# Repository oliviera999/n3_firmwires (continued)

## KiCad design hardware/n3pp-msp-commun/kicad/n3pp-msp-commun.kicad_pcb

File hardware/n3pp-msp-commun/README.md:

# Carte commune n3pp + msp (KiCad)

**Un seul PCB pour deux stations** : la serre/élevage (**n3pp**) et la station météo
(**msp**) partagent cette carte porteuse pour **ESP32 DevKit V1 30 broches**. Les deux
brochages firmware forment une **union disjointe vérifiée** (aucun GPIO utilisé pour deux
usages différents) : les firmwares actuels tournent **sans aucune modification**, c'est le
**profil d'assemblage** (quels composants on soude) qui spécialise la carte.

```
pinmap.json                  Source de vérité (union n3pp_config.h + msp_config.h, profils par broche)
kicad/n3pp-msp-commun.*      Projet KiCad 8 (schéma, PCB ROUTÉ) — ouvrable KiCad 8/9/10
BOM.csv                      Nomenclature (séparateur ;) avec colonne Profil
ACHATS.md                    Liste d'achat complète par profil (BOM + périphériques + boîtier + outillage)
ASSEMBLAGE-N3PP.md           Feuille d'assemblage générée : quoi souder pour une station n3pp
ASSEMBLAGE-MSP.md            Feuille d'assemblage générée : quoi souder pour une station msp
exports/gerbers-*.zip        Fabrication (Gerbers + perçages) — 210 x 105 mm, 2 couches, rev 0.2
exports/schema.pdf, pcb-*.svg   Rendus pour revue sans KiCad
fritzing/*.fzz               Vue breadboard du câblage (Fritzing >= 1.0)
generator/generate.py        Régénère schéma + PCB (non routé) + BOM + feuilles d'assemblage
generator/route_lv.py        Pipeline de routage (freerouting + couture GND + reliefs)
generator/tidy_silkscreen.py  Range la sérigraphie (repères vs étiquettes)
generator/export_fab.py      Export Gerbers/perçages prêts fabricant + rendus
generator/generate_fritzing.py  Régénère le .fzz de câblage
tools/check_pinmap_vs_firmware.py   Garde anti-dérive DOUBLE : n3pp_config.h ET msp_config.h ↔ plan
```

## Le principe : une base, deux profils

| Profil | Composants à souder | Le firmware tourne tel quel ? |
|---|---|---|
| **commun** | DevKit + alim + **interrupteur d'alim capteurs (GPIO13)** + 5 entrées ADC + pont batterie commuté + I2C/OLED + breakout + distribution | — (socle des deux profils) |
| **n3pp** | + REL2 (pompe GPIO12) + DHT GPIO18 | ✅ `pio run -e esp32dev` (n3pp) |
| **msp** | + servos tracker + 2 DHT + DS18B20 + pluie + 10k LDR | ✅ `pio run -e esp32dev` (msp) |
| **extension** | REL3..REL6 (GPIO 16/17/19/23), à activer côté firmware plus tard | provision matérielle |

Aucun strap, aucun interrupteur : les GPIO des deux firmwares ne se marchent jamais
dessus (voir la table ci-dessous), on peuple ou pas. Les feuilles
[`ASSEMBLAGE-N3PP.md`](ASSEMBLAGE-N3PP.md) / [`ASSEMBLAGE-MSP.md`](ASSEMBLAGE-MSP.md)
sont **générées depuis le même code que le PCB** : elles ne peuvent pas dériver du plan.

## Table des broches (union disjointe)

| GPIO | Bloc carte | n3pp (`n3pp_config.h`) | msp (`msp_config.h`) |
|---|---|---|---|
| 13 | **Interrupteur d'alim capteurs** (Q1+Q7 P-MOSFET → rail `+3V3_SW`) | `RELAIS` | `RELAIS` |
| 12 | **REL2** (strapping MTDI → pull-down base 10k) | `POMPE` | — |
| 16/17/19/23 | **REL3..REL6** extensions AUX | — | — |
| 18 | DHT n3pp (JST, pull-up 10k) | `DHTPIN` | — |
| 26 / 15 | DHT INT / EXT (JST, pull-ups 10k) | — | `DHTPININT` / `DHTPINEXT` |
| 2 | 1-Wire DS18B20 (bornier, pull-up 4,7k) ⚠️ strapping | — | `oneWireBus` |
| 27 | Pluie — **sortie DO numérique** (ADC2 ≠ WiFi) | — | `PLUIE` |
| 33/32/35/34/39 | **ADC A..E** (borniers 3V3/AIN/GND) | `humidite1..4`, `LUMINOSITE` | `LUMINOSITEa..d`, `HumiditeSol` |
| 36 (VP) | Pont batterie 2,2k/2,2k (bornier VBAT/GND) | `pontdiv` | `pontdiv` |
| 25 / 14 | Servos tracker (headers, série 220R) | — | `SERVOGD` / `SERVOHB` |
| 21 / 22 | I2C : OLED 0x3C + **3 ports libres** (pull-ups 4,7k) | ✅ | ✅ |
| 4, 5, EN, RX0, TX0 | **Breakout J18** (tous les GPIO restants) | libres | libres |

## Les demandes spécifiques de cette carte

- **Rail capteurs commuté (rev 0.2)** : les deux firmwares utilisent GPIO13 comme
  *power-gate* (mis à 1 au réveil, relâché en deep sleep — vérifié dans les sources).
  La carte le câble sur un **interrupteur haut P-MOSFET** (Q1 BC337 + Q7 NDP6020P) qui
  coupe `+3V3_SW` — capteurs, OLED, ports I2C **et leurs pull-ups** — pendant la veille.
  Le **pont diviseur batterie est commuté lui aussi** (Q8 BS250 côté haut + Q9), donc
  ~0 µA de fuite en veille, et jamais plus de 3,3 V sur GPIO36 pont coupé.
- **5 canaux relais** embarqués (BC337 + 1N4007 + LED témoin + bornier NO/COM/NC) :
  REL2 piloté par n3pp (pompe), REL3..REL6 en réserve sur des GPIO **non-strapping** —
  à activer côté firmware comme AUX1/AUX2 de ffp5cs, sans retoucher la carte.
- **Connexions I2C supplémentaires** : OLED + 3 ports libres (J15/J16/J17, brochage
  GND/VCC/SCL/SDA), 3-4 modules simultanés avec les pull-ups 4,7 k.
- **Toutes les broches restantes utilisables** : breakout J18 (`3V3 GND EN IO4 IO5 RX0
  TX0` — RX0/TX0 à laisser libres pendant un flash USB), rail d'alim Dupont J19
  (2×5V 2×GND 2×3V3), borniers de distribution 5 V (J28) et 3V3 (J29).
- **Zéro soudure à l'usage** : DevKit socketé, charges sur borniers à vis, capteurs sur
  JST-XH/borniers, servos/OLED/GPIO en headers.

## Pièges connus (hérités des firmwares, choix assumés)

- **GPIO2 (1-Wire msp)** est une broche de strapping : le pull-up 4,7 k peut gêner le
  passage en mode flash. Si le flash USB échoue, débrancher la sonde DS18B20 le temps du
  flash. (Conservé pour rester compatible avec le firmware msp actuel.)
- **GPIO27 (pluie msp)** est sur ADC2, inutilisable en analogique quand le WiFi est actif :
  brancher la sortie **DO** (numérique) du module pluie, pas AO — lue en `digitalRead`
  par le firmware msp ≥ 2.72 (projection 4095 sec / 100 mouillé, contrat serveur inchangé).
- **GPIO12 (pompe n3pp)** est strapping MTDI : le pull-down de base du canal REL2 garantit
  l'état sûr au boot.
- **JP1 (cavalier 3V3)** : en alimentation batterie/LDO par J29, RETIRER le cavalier
  avant de brancher l'USB du DevKit (sinon deux régulateurs se disputent le rail).
- Profils **sur batterie (18650 + TP4056 solaire)** : ne pas peupler les LED témoin,
  et **ne jamais brancher la batterie brute sur J1/jack** (brownouts + relais 5 V) —
  boost 5 V → J1 si relais/servos, ou LDO 3,3 V → J29 sinon ; mesure VBAT → J27.
  Câblages, achats et autonomies chiffrées : [`ACHATS.md` §5 bis](ACHATS.md).

## Régénérer / rerouter / vérifier

```bash
cd hardware/n3pp-msp-commun
python3 generator/generate.py          # schéma + PCB placé (NON routé) + BOM + feuilles
python3 generator/route_lv.py          # autoroute, coud les masses, corrige les reliefs
python3 generator/tidy_silkscreen.py   # écarte les repères qui masquent une étiquette
python3 generator/export_fab.py        # zip Gerbers prêt JLCPCB + rendus de revue
python3 tools/check_pinmap_vs_firmware.py   # garde anti-dérive (les DEUX firmwares)
kicad-cli pcb drc --severity-error kicad/n3pp-msp-commun.kicad_pcb -o /tmp/drc.rpt
```

⚠️ `generate.py` écrase le PCB routé — enchaîner systématiquement avec `route_lv.py`.
Le routage livré dans `kicad/` est déjà fait et validé (DRC 0 violation).

Empreintes : bibliothèque officielle KiCad 8.0.9 (CC-BY-SA 4.0 + exception d'usage),
vendorées dans `generator/footprints/`.

Commander les cartes : voir **[../COMMANDE_JLCPCB.md](../COMMANDE_JLCPCB.md)**
(réglages du formulaire, options utiles, pourquoi 1 oz ici et 2 oz sur la 230 V).

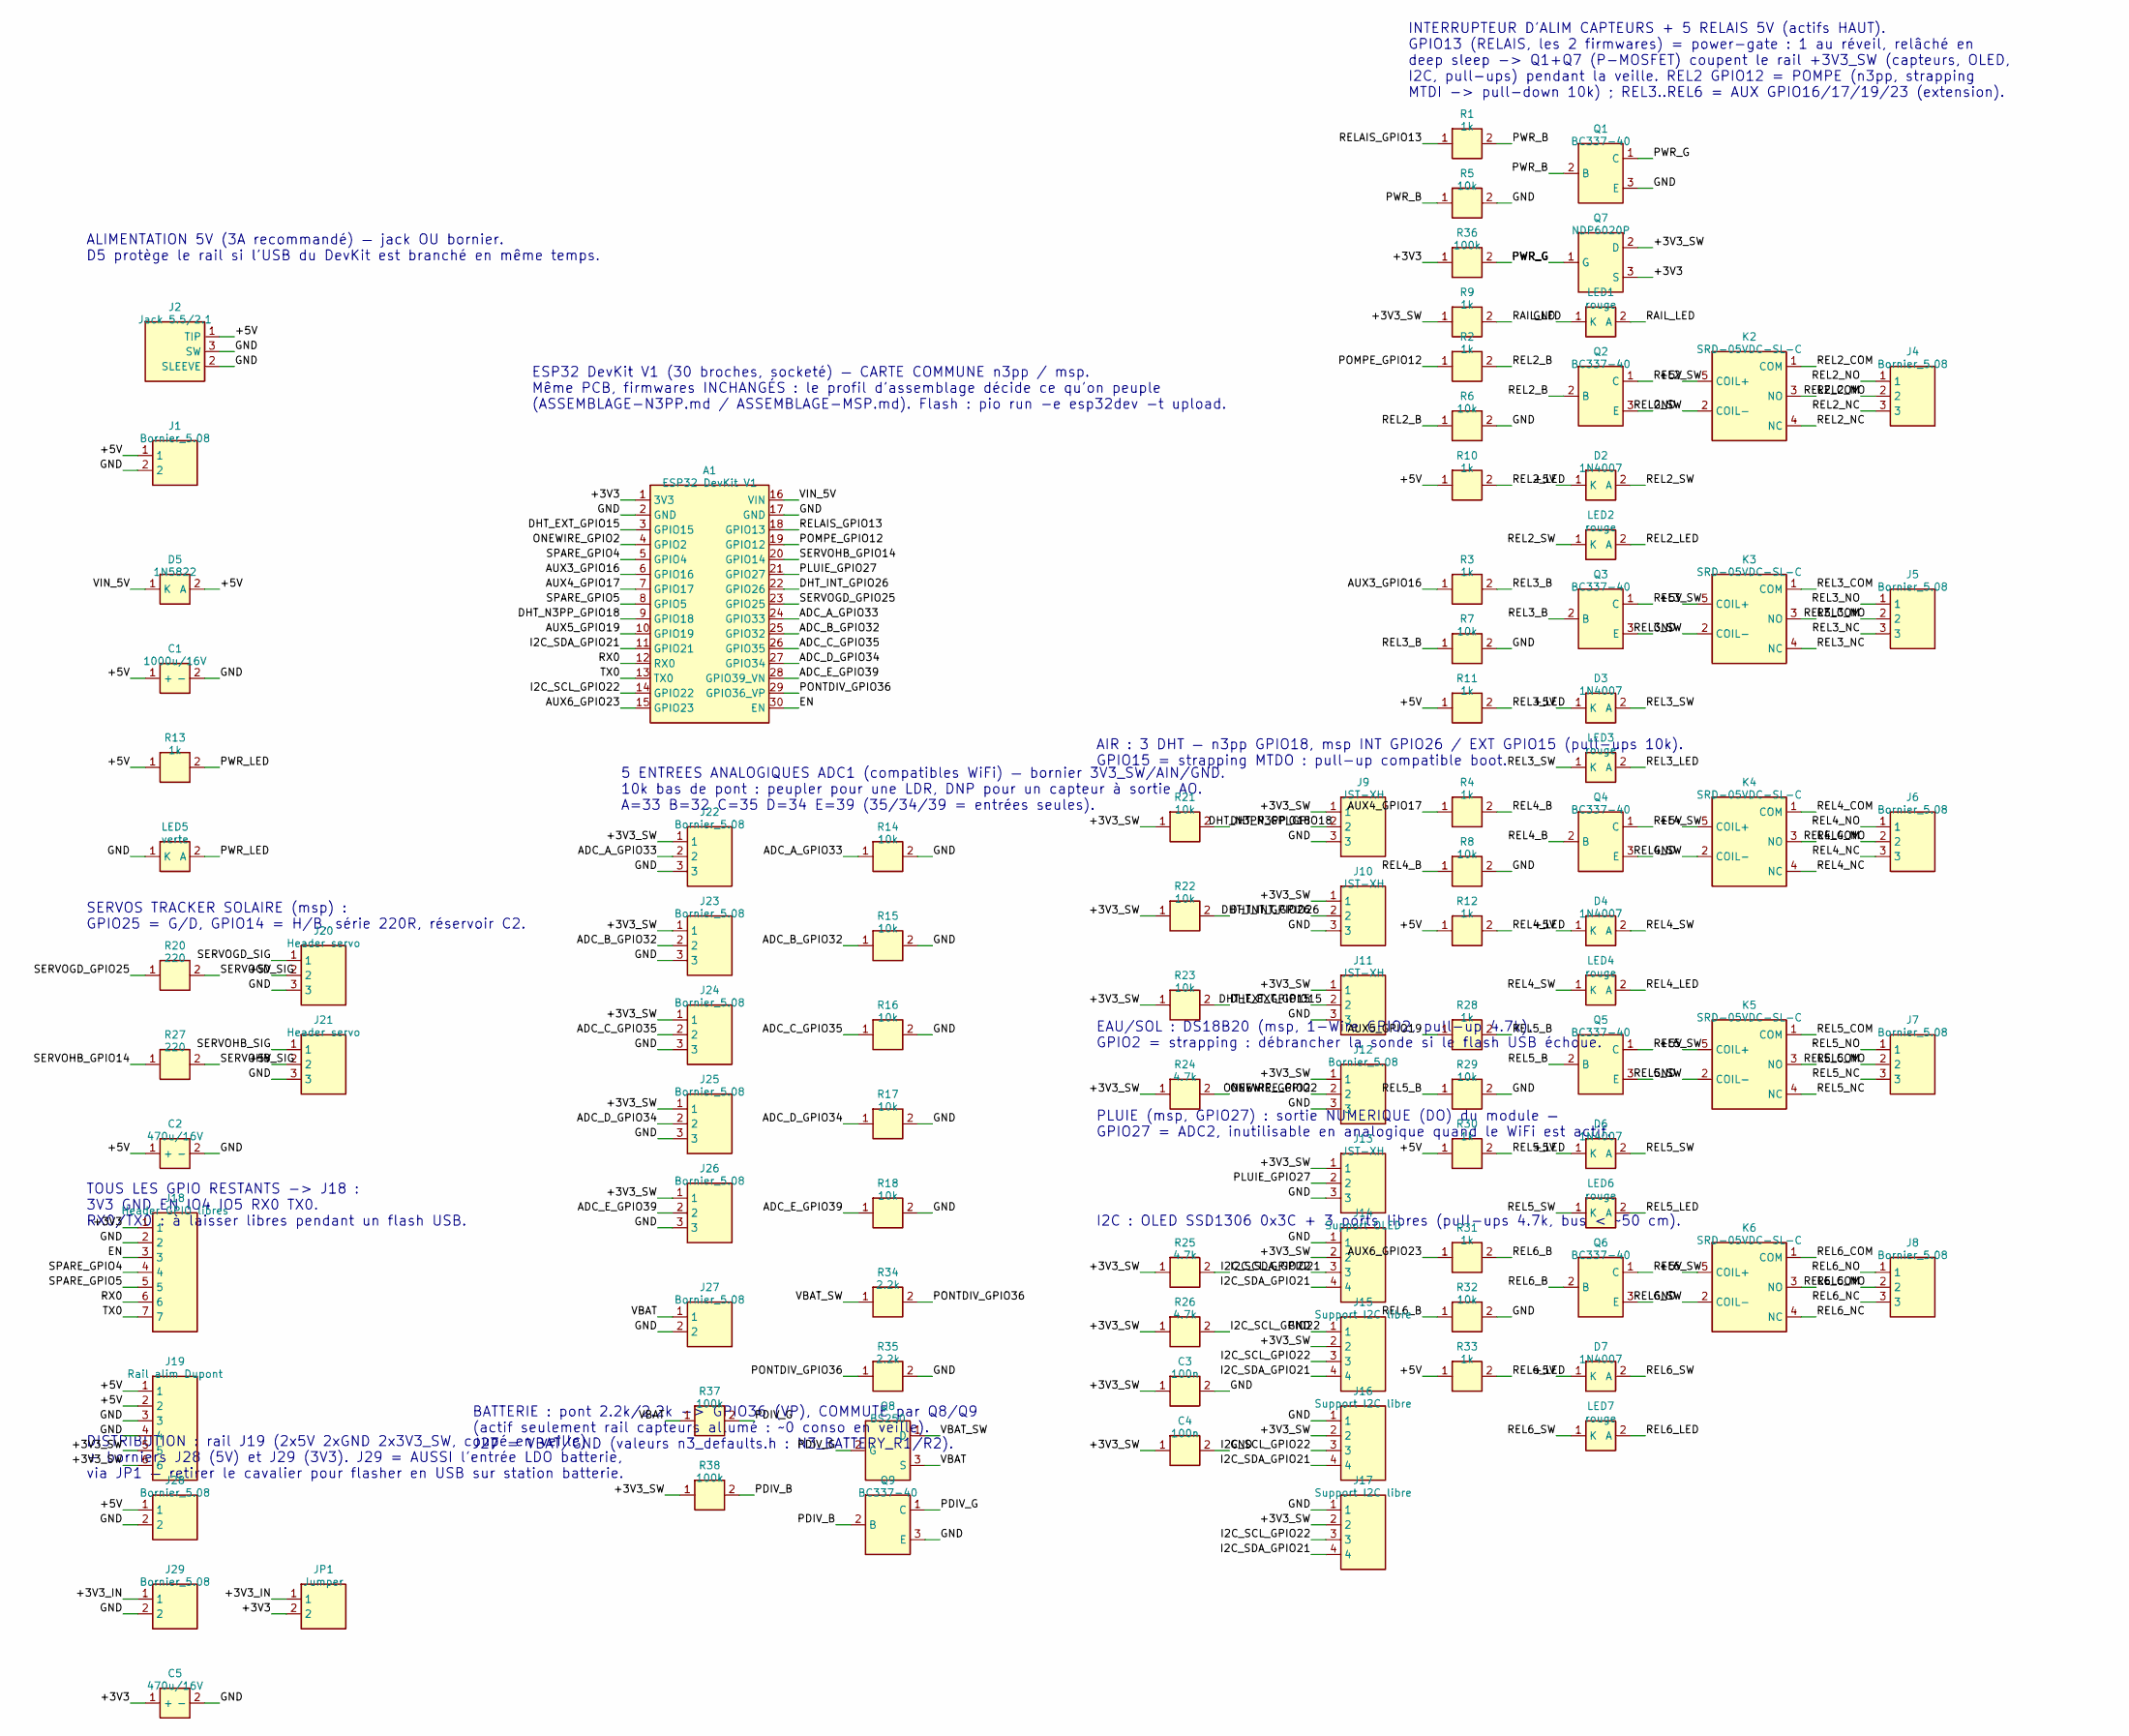
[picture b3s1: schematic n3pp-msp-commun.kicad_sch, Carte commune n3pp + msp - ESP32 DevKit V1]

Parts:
A1: ESP32 DevKit V1; ESP32_DevKit_V1_30pin
C1: 1000u/16V; CP_Radial_D10.0mm_P5.00mm
C2, C5: 470u/16V; CP_Radial_D8.0mm_P3.50mm
C3, C4: 100n; C_Disc_D5.0mm_W2.5mm_P5.00mm
D2, D3, D4, D6, D7: 1N4007; D_DO-41_SOD81_P10.16mm_Horizontal
D5: 1N5822; D_DO-201AD_P15.24mm_Horizontal
J1, J27, J28, J29: Bornier_5.08; TerminalBlock_bornier-2_P5.08mm
J2: Jack 5.5/2.1; BarrelJack_Horizontal
J4, J5, J6, J7, J8, J12, J22, J23, J24, J25, J26: Bornier_5.08; TerminalBlock_bornier-3_P5.08mm
J9, J10, J11, J13: JST-XH; JST_XH_B3B-XH-A_1x03_P2.50mm_Vertical
J14: Support OLED; PinSocket_1x04_P2.54mm_Vertical
J15, J16, J17: Support I2C libre; PinSocket_1x04_P2.54mm_Vertical
J18: Header GPIO libres; PinHeader_1x07_P2.54mm_Vertical
J19: Rail alim Dupont; PinHeader_1x06_P2.54mm_Vertical
J20, J21: Header servo; PinHeader_1x03_P2.54mm_Vertical
JP1: Jumper; PinHeader_1x02_P2.54mm_Vertical
K2, K3, K4, K5, K6: SRD-05VDC-SL-C; Relay_SPDT_SANYOU_SRD_Series_Form_C
LED1, LED2, LED3, LED4, LED6, LED7: rouge; LED_D5.0mm
LED5: verte; LED_D5.0mm
Q1, Q2, Q3, Q4, Q5, Q6, Q9: BC337-40; TO-92_Inline
Q7: NDP6020P; TO-220-3_Vertical
Q8: BS250; TO-92_Inline
R1, R2, R3, R4, R9, R10, R11, R12, R13, R28, R30, R31, R33: 1k; R_Axial_DIN0207_L6.3mm_D2.5mm_P10.16mm_Horizontal
R5, R6, R7, R8, R14, R15, R16, R17, R18, R21, R22, R23, R29, R32: 10k; R_Axial_DIN0207_L6.3mm_D2.5mm_P10.16mm_Horizontal
R20, R27: 220; R_Axial_DIN0207_L6.3mm_D2.5mm_P10.16mm_Horizontal
R24, R25, R26: 4.7k; R_Axial_DIN0207_L6.3mm_D2.5mm_P10.16mm_Horizontal
R34, R35: 2.2k; R_Axial_DIN0207_L6.3mm_D2.5mm_P10.16mm_Horizontal
R36, R37, R38: 100k; R_Axial_DIN0207_L6.3mm_D2.5mm_P10.16mm_Horizontal

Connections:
+3V3: A1.1 (3V3), C5.1 (+), J18.1, JP1.2, Q7.3 (S), R36.1
+3V3_IN: J29.1, JP1.1
+3V3_SW: C3.1, C4.1, J9.1, J10.1, J11.1, J12.1, J13.1, J14.2, J15.2, J16.2, J17.2, J19.5, J19.6, J22.1, J23.1, J24.1, J25.1, J26.1, Q7.2 (D), R9.1, R21.1, R22.1, R23.1, R24.1, R25.1, R26.1, R38.1
+5V: C1.1 (+), C2.1 (+), D2.1 (K), D3.1 (K), D4.1 (K), D5.2 (A), D6.1 (K), D7.1 (K), J1.1, J2.1 (TIP), J19.1, J19.2, J20.2, J21.2, J28.1, K2.5 (COIL+), K3.5 (COIL+), K4.5 (COIL+), K5.5 (COIL+), K6.5 (COIL+), R10.1, R11.1, R12.1, R13.1, R30.1, R33.1
ADC_A_GPIO33: A1.24 (GPIO33), J22.2, R14.1
ADC_B_GPIO32: A1.25 (GPIO32), J23.2, R15.1
ADC_C_GPIO35: A1.26 (GPIO35), J24.2, R16.1
ADC_D_GPIO34: A1.27 (GPIO34), J25.2, R17.1
ADC_E_GPIO39: A1.28 (GPIO39_VN), J26.2, R18.1
AUX3_GPIO16: A1.6 (GPIO16), R3.1
AUX4_GPIO17: A1.7 (GPIO17), R4.1
AUX5_GPIO19: A1.10 (GPIO19), R28.1
AUX6_GPIO23: A1.15 (GPIO23), R31.1
DHT_EXT_GPIO15: A1.3 (GPIO15), J11.2, R23.2
DHT_INT_GPIO26: A1.22 (GPIO26), J10.2, R22.2
DHT_N3PP_GPIO18: A1.9 (GPIO18), J9.2, R21.2
EN: A1.30 (EN), J18.3
GND: A1.2 (GND), A1.17 (GND), C1.2 (-), C2.2 (-), C3.2, C4.2, C5.2 (-), J1.2, J2.2 (SLEEVE), J2.3 (SW), J9.3, J10.3, J11.3, J12.3, J13.3, J14.1, J15.1, J16.1, J17.1, J18.2, J19.3, J19.4, J20.3, J21.3, J22.3, J23.3, J24.3, J25.3, J26.3, J27.2, J28.2, J29.2, LED1.1 (K), LED5.1 (K), Q1.3 (E), Q2.3 (E), Q3.3 (E), Q4.3 (E), Q5.3 (E), Q6.3 (E), Q9.3 (E), R5.2, R6.2, R7.2, R8.2, R14.2, R15.2, R16.2, R17.2, R18.2, R29.2, R32.2, R35.2
I2C_SCL_GPIO22: A1.14 (GPIO22), J14.3, J15.3, J16.3, J17.3, R26.2
I2C_SDA_GPIO21: A1.11 (GPIO21), J14.4, J15.4, J16.4, J17.4, R25.2
ONEWIRE_GPIO2: A1.4 (GPIO2), J12.2, R24.2
PDIV_B: Q9.2 (B), R38.2
PDIV_G: Q8.2 (G), Q9.1 (C), R37.2
PLUIE_GPIO27: A1.21 (GPIO27), J13.2
POMPE_GPIO12: A1.19 (GPIO12), R2.1
PONTDIV_GPIO36: A1.29 (GPIO36_VP), R34.2, R35.1
PWR_B: Q1.2 (B), R1.2, R5.1
PWR_G: Q1.1 (C), Q7.1 (G), R36.2
PWR_LED: LED5.2 (A), R13.2
RAIL_LED: LED1.2 (A), R9.2
REL2_B: Q2.2 (B), R2.2, R6.1
REL2_COM: J4.2, K2.1 (COM)
REL2_LED: LED2.2 (A), R10.2
REL2_NC: J4.3, K2.4 (NC)
REL2_NO: J4.1, K2.3 (NO)
REL2_SW: D2.2 (A), K2.2 (COIL-), LED2.1 (K), Q2.1 (C)
REL3_B: Q3.2 (B), R3.2, R7.1
REL3_COM: J5.2, K3.1 (COM)
REL3_LED: LED3.2 (A), R11.2
REL3_NC: J5.3, K3.4 (NC)
REL3_NO: J5.1, K3.3 (NO)
REL3_SW: D3.2 (A), K3.2 (COIL-), LED3.1 (K), Q3.1 (C)
REL4_B: Q4.2 (B), R4.2, R8.1
REL4_COM: J6.2, K4.1 (COM)
REL4_LED: LED4.2 (A), R12.2
REL4_NC: J6.3, K4.4 (NC)
REL4_NO: J6.1, K4.3 (NO)
REL4_SW: D4.2 (A), K4.2 (COIL-), LED4.1 (K), Q4.1 (C)
REL5_B: Q5.2 (B), R28.2, R29.1
REL5_COM: J7.2, K5.1 (COM)
REL5_LED: LED6.2 (A), R30.2
REL5_NC: J7.3, K5.4 (NC)
REL5_NO: J7.1, K5.3 (NO)
REL5_SW: D6.2 (A), K5.2 (COIL-), LED6.1 (K), Q5.1 (C)
REL6_B: Q6.2 (B), R31.2, R32.1
REL6_COM: J8.2, K6.1 (COM)
REL6_LED: LED7.2 (A), R33.2
REL6_NC: J8.3, K6.4 (NC)
REL6_NO: J8.1, K6.3 (NO)
REL6_SW: D7.2 (A), K6.2 (COIL-), LED7.1 (K), Q6.1 (C)
RELAIS_GPIO13: A1.18 (GPIO13), R1.1
RX0: A1.12 (RX0), J18.6
SERVOGD_GPIO25: A1.23 (GPIO25), R20.1
SERVOGD_SIG: J20.1, R20.2
SERVOHB_GPIO14: A1.20 (GPIO14), R27.1
SERVOHB_SIG: J21.1, R27.2
SPARE_GPIO4: A1.5 (GPIO4), J18.4
SPARE_GPIO5: A1.8 (GPIO5), J18.5
TX0: A1.13 (TX0), J18.7
VBAT: J27.1, Q8.3 (S), R37.1
VBAT_SW: Q8.1 (D), R34.1
VIN_5V: A1.16 (VIN), D5.1 (K)

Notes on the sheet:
ALIMENTATION 5V (3A recommandé) — jack OU bornier. D5 protège le rail si l'USB du DevKit est branché en même temps.
ESP32 DevKit V1 (30 broches, socketé) — CARTE COMMUNE n3pp / msp. Même PCB, firmwares INCHANGÉS : le profil d'assemblage décide ce qu'on peuple (ASSEMBLAGE-N3PP.md / ASSEMBLAGE-MSP.md). Flash : pio run -e esp32dev -t upload.
5 ENTREES ANALOGIQUES ADC1 (compatibles WiFi) — bornier 3V3_SW/AIN/GND. 10k bas de pont : peupler pour une LDR, DNP pour un capteur à sortie AO. A=33 B=32 C=35 D=34 E=39 (35/34/39 = entrées seules).
BATTERIE : pont 2.2k/2.2k -> GPIO36 (VP), COMMUTE par Q8/Q9 (actif seulement rail capteurs allumé : ~0 conso en veille). J27 = VBAT/GND (valeurs n3_defaults.h : N3_BATTERY_R1/R2).
SERVOS TRACKER SOLAIRE (msp) : GPIO25 = G/D, GPIO14 = H/B, série 220R, réservoir C2.
TOUS LES GPIO RESTANTS -> J18 : 3V3 GND EN IO4 IO5 RX0 TX0. RX0/TX0 : à laisser libres pendant un flash USB.
DISTRIBUTION : rail J19 (2x5V 2xGND 2x3V3_SW, coupé en veille) + borniers J28 (5V) et J29 (3V3). J29 = AUSSI l'entrée LDO batterie, via JP1 — retirer le cavalier pour flasher en USB sur station batterie.
AIR : 3 DHT — n3pp GPIO18, msp INT GPIO26 / EXT GPIO15 (pull-ups 10k). GPIO15 = strapping MTDO : pull-up compatible boot.
EAU/SOL : DS18B20 (msp, 1-Wire GPIO2, pull-up 4.7k). GPIO2 = strapping : débrancher la sonde si le flash USB échoue.
PLUIE (msp, GPIO27) : sortie NUMERIQUE (DO) du module — GPIO27 = ADC2, inutilisable en analogique quand le WiFi est actif.
I2C : OLED SSD1306 0x3C + 3 ports libres (pull-ups 4.7k, bus < ~50 cm).
INTERRUPTEUR D'ALIM CAPTEURS + 5 RELAIS 5V (actifs HAUT). GPIO13 (RELAIS, les 2 firmwares) = power-gate : 1 au réveil, relâché en deep sleep -> Q1+Q7 (P-MOSFET) coupent le rail +3V3_SW (capteurs, OLED, I2C, pull-ups) pendant la veille. REL2 GPIO12 = POMPE (n3pp, strapping MTDI -> pull-down 10k) ; R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

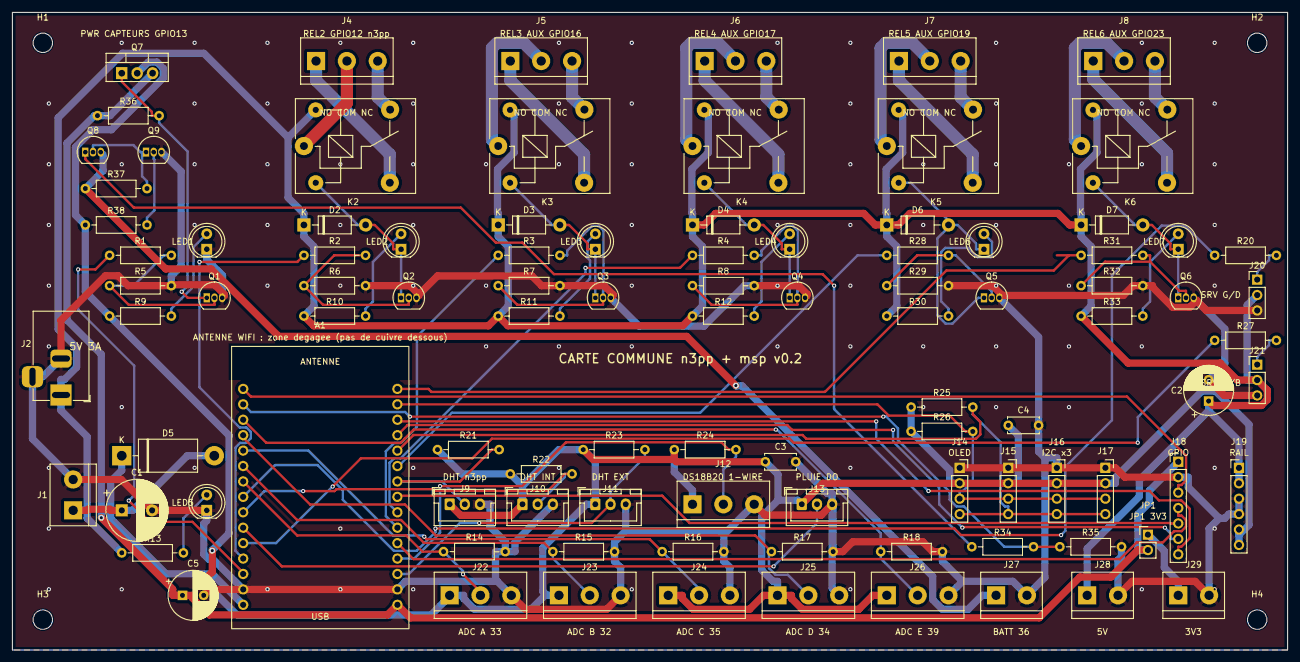
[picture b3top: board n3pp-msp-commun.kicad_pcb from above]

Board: 2 copper layers, 210.0 x 105.0 mm, 103 parts (0 on the bottom side), 72 nets.

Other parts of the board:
H1, H2, H3, H4: M3; MountingHole_3.2mm_M3

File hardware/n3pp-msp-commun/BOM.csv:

Refs;Qte;Valeur;Empreinte;Description;Profil
A1;1;ESP32 DevKit V1;ESP32_DevKit_V1_30pin;Module ESP32-WROOM-32 DevKit V1 30 broches, sur 2 supports 1x15;commun (toujours)
C1;1;1000u/16V;CP_Radial_D10.0mm_P5.00mm;Réservoir rail 5V (relais + servos + WiFi);commun (toujours)
C2;1;470u/16V;CP_Radial_D8.0mm_P3.50mm;Découplage rail 5V servos;profil msp
C3;1;100n;C_Disc_D5.0mm_W2.5mm_P5.00mm;Découplage 3V3 capteurs;commun (toujours)
C4;1;100n;C_Disc_D5.0mm_W2.5mm_P5.00mm;Découplage 3V3 I2C;commun (toujours)
D1;1;1N4007;D_DO-41_SOD81_P10.16mm_Horizontal;Diode de roue libre bobine;commun (toujours)
D2;1;1N4007;D_DO-41_SOD81_P10.16mm_Horizontal;Diode de roue libre bobine;profil n3pp
D3 D4 D6 D7;4;1N4007;D_DO-41_SOD81_P10.16mm_Horizontal;Diode de roue libre bobine;extension (option)
D5;1;1N5822;D_DO-201AD_P15.24mm_Horizontal;Schottky 3A vers VIN DevKit (anti-retour si USB branché);commun (toujours)
H1 H2 H3 H4;4;M3;MountingHole_3.2mm_M3;Trou de fixation M3;commun (toujours)
J1;1;Bornier_5.08;TerminalBlock_bornier-2_P5.08mm;Entrée 5V alternative (bornier, 1=+5V 2=GND);commun (toujours)
J10;1;JST-XH;JST_XH_B3B-XH-A_1x03_P2.50mm_Vertical;DHT INT msp (1=3V3 2=DATA 3=GND);profil msp
J11;1;JST-XH;JST_XH_B3B-XH-A_1x03_P2.50mm_Vertical;DHT EXT msp (1=3V3 2=DATA 3=GND);profil msp
J12;1;Bornier_5.08;TerminalBlock_bornier-3_P5.08mm;Sonde DS18B20 étanche (1=3V3 2=DATA 3=GND);profil msp
J13;1;JST-XH;JST_XH_B3B-XH-A_1x03_P2.50mm_Vertical;Capteur pluie — sortie NUMERIQUE DO (1=3V3 2=DO 3=GND);profil msp
J14;1;Support OLED;PinSocket_1x04_P2.54mm_Vertical;OLED SSD1306 128x64 I2C 0x3C (1=GND 2=VCC 3=SCL 4=SDA);commun (toujours)
J15;1;Support I2C libre;PinSocket_1x04_P2.54mm_Vertical;Port I2C libre 1 (1=GND 2=VCC 3=SCL 4=SDA);commun (toujours)
J16;1;Support I2C libre;PinSocket_1x04_P2.54mm_Vertical;Port I2C libre 2 (1=GND 2=VCC 3=SCL 4=SDA);commun (toujours)
J17;1;Support I2C libre;PinSocket_1x04_P2.54mm_Vertical;Port I2C libre 3 (1=GND 2=VCC 3=SCL 4=SDA);commun (toujours)
J18;1;Header GPIO libres;PinHeader_1x07_P2.54mm_Vertical;GPIO libres (1=3V3 2=GND 3=EN 4=IO4 5=IO5 6=RX0 7=TX0);commun (toujours)
J19;1;Rail alim Dupont;PinHeader_1x06_P2.54mm_Vertical;Rail alim modules (1=5V 2=5V 3=GND 4=GND 5=3V3 6=3V3);commun (toujours)
J2;1;Jack 5.5/2.1;BarrelJack_Horizontal;Entrée 5V 3A (jack, centre = +);commun (toujours)
J20;1;Header servo;PinHeader_1x03_P2.54mm_Vertical;Servo G/D tracker (1=SIG 2=+5V 3=GND);profil msp
J21;1;Header servo;PinHeader_1x03_P2.54mm_Vertical;Servo H/B tracker (1=SIG 2=+5V 3=GND);profil msp
J22;1;Bornier_5.08;TerminalBlock_bornier-3_P5.08mm;Entrée ADC_A (1=3V3 2=AIN 3=GND) — n3pp: humidite1 (sol) / msp: LUMINOSITEa (LDR);commun (toujours)
J23;1;Bornier_5.08;TerminalBlock_bornier-3_P5.08mm;Entrée ADC_B (1=3V3 2=AIN 3=GND) — n3pp: humidite2 (sol) / msp: HumiditeSol (module AO);commun (toujours)
J24;1;Bornier_5.08;TerminalBlock_bornier-3_P5.08mm;Entrée ADC_C (1=3V3 2=AIN 3=GND) — n3pp: humidite3 (sol) / msp: LUMINOSITEc (LDR);commun (toujours)
J25;1;Bornier_5.08;TerminalBlock_bornier-3_P5.08mm;Entrée ADC_D (1=3V3 2=AIN 3=GND) — n3pp: humidite4 (sol) / msp: LUMINOSITEb (LDR);commun (toujours)
J26;1;Bornier_5.08;TerminalBlock_bornier-3_P5.08mm;Entrée ADC_E (1=3V3 2=AIN 3=GND) — n3pp: LUMINOSITE (LDR) / msp: LUMINOSITEd (LDR);commun (toujours)
J27;1;Bornier_5.08;TerminalBlock_bornier-2_P5.08mm;Mesure batterie (1=VBAT 2=GND, pont 2.2k/2.2k -> GPIO36);commun (toujours)
J28;1;Bornier_5.08;TerminalBlock_bornier-2_P5.08mm;Distribution 5V (1=+5V 2=GND);commun (toujours)
J29;1;Bornier_5.08;TerminalBlock_bornier-2_P5.08mm;Distribution 3V3 (1=+3V3 2=GND);commun (toujours)
J3;1;Bornier_5.08;TerminalBlock_bornier-3_P5.08mm;Bornier charge (1=NO 2=COM 3=NC);commun (toujours)
J4;1;Bornier_5.08;TerminalBlock_bornier-3_P5.08mm;Bornier charge (1=NO 2=COM 3=NC);profil n3pp
J5 J6 J7 J8;4;Bornier_5.08;TerminalBlock_bornier-3_P5.08mm;Bornier charge (1=NO 2=COM 3=NC);extension (option)
J9;1;JST-XH;JST_XH_B3B-XH-A_1x03_P2.50mm_Vertical;DHT n3pp (1=3V3 2=DATA 3=GND);profil n3pp
K1;1;SRD-05VDC-SL-C;Relay_SPDT_SANYOU_SRD_Series_Form_C;Relais 5V SPDT 10A (Songle/Sanyou SRD);commun (toujours)
K2;1;SRD-05VDC-SL-C;Relay_SPDT_SANYOU_SRD_Series_Form_C;Relais 5V SPDT 10A (Songle/Sanyou SRD);profil n3pp
K3 K4 K5 K6;4;SRD-05VDC-SL-C;Relay_SPDT_SANYOU_SRD_Series_Form_C;Relais 5V SPDT 10A (Songle/Sanyou SRD);extension (option)
LED1;1;rouge;LED_D5.0mm;LED témoin relais ON (DNP si profil batterie);commun (toujours)
LED2;1;rouge;LED_D5.0mm;LED témoin relais ON (DNP si profil batterie);profil n3pp
LED3 LED4 LED6 LED7;4;rouge;LED_D5.0mm;LED témoin relais ON (DNP si profil batterie);extension (option)
LED5;1;verte;LED_D5.0mm;LED présence 5V (DNP si profil batterie);commun (toujours)
Q1;1;BC337-40;TO-92_Inline;Transistor NPN commande relais (1=C 2=B 3=E);commun (toujours)
Q2;1;BC337-40;TO-92_Inline;Transistor NPN commande relais (1=C 2=B 3=E);profil n3pp
Q3 Q4 Q5 Q6;4;BC337-40;TO-92_Inline;Transistor NPN commande relais (1=C 2=B 3=E);extension (option)
R1;1;1k;R_Axial_DIN0207_L6.3mm_D2.5mm_P10.16mm_Horizontal;Résistance base transistor;commun (toujours)
R10;1;1k;R_Axial_DIN0207_L6.3mm_D2.5mm_P10.16mm_Horizontal;Résistance LED témoin (DNP si profil batterie);profil n3pp
R11 R12 R30 R33;4;1k;R_Axial_DIN0207_L6.3mm_D2.5mm_P10.16mm_Horizontal;Résistance LED témoin (DNP si profil batterie);extension (option)
R13;1;1k;R_Axial_DIN0207_L6.3mm_D2.5mm_P10.16mm_Horizontal;Résistance LED présence 5V (DNP si profil batterie);commun (toujours)
R14;1;10k;R_Axial_DIN0207_L6.3mm_D2.5mm_P10.16mm_Horizontal;"Bas de pont ADC_A (peupler si LDR ; DNP si capteur AO)";profil msp
R15;1;10k;R_Axial_DIN0207_L6.3mm_D2.5mm_P10.16mm_Horizontal;"Bas de pont ADC_B (peupler si LDR ; DNP si capteur AO)";extension (option)
R16;1;10k;R_Axial_DIN0207_L6.3mm_D2.5mm_P10.16mm_Horizontal;"Bas de pont ADC_C (peupler si LDR ; DNP si capteur AO)";profil msp
R17;1;10k;R_Axial_DIN0207_L6.3mm_D2.5mm_P10.16mm_Horizontal;"Bas de pont ADC_D (peupler si LDR ; DNP si capteur AO)";profil msp
R18;1;10k;R_Axial_DIN0207_L6.3mm_D2.5mm_P10.16mm_Horizontal;"Bas de pont ADC_E (peupler si LDR ; DNP si capteur AO)";commun (toujours)
R2;1;1k;R_Axial_DIN0207_L6.3mm_D2.5mm_P10.16mm_Horizontal;Résistance base transistor;profil n3pp
R20;1;220;R_Axial_DIN0207_L6.3mm_D2.5mm_P10.16mm_Horizontal;Série signal servo G/D (GPIO25);profil msp
R21;1;10k;R_Axial_DIN0207_L6.3mm_D2.5mm_P10.16mm_Horizontal;Pull-up data DHT n3pp;profil n3pp
R22;1;10k;R_Axial_DIN0207_L6.3mm_D2.5mm_P10.16mm_Horizontal;Pull-up data DHT INT msp;profil msp
R23;1;10k;R_Axial_DIN0207_L6.3mm_D2.5mm_P10.16mm_Horizontal;Pull-up data DHT EXT msp;profil msp
R24;1;4.7k;R_Axial_DIN0207_L6.3mm_D2.5mm_P10.16mm_Horizontal;Pull-up bus 1-Wire DS18B20;profil msp
R25;1;4.7k;R_Axial_DIN0207_L6.3mm_D2.5mm_P10.16mm_Horizontal;Pull-up I2C SDA;commun (toujours)
R26;1;4.7k;R_Axial_DIN0207_L6.3mm_D2.5mm_P10.16mm_Horizontal;Pull-up I2C SCL;commun (toujours)
R27;1;220;R_Axial_DIN0207_L6.3mm_D2.5mm_P10.16mm_Horizontal;Série signal servo H/B (GPIO14);profil msp
R28 R3 R31 R4;4;1k;R_Axial_DIN0207_L6.3mm_D2.5mm_P10.16mm_Horizontal;Résistance base transistor;extension (option)
R34;1;2.2k;R_Axial_DIN0207_L6.3mm_D2.5mm_P10.16mm_Horizontal;Pont batterie haut (N3_BATTERY_R1=2200);commun (toujours)
R35;1;2.2k;R_Axial_DIN0207_L6.3mm_D2.5mm_P10.16mm_Horizontal;Pont batterie bas (N3_BATTERY_R2=2180, 2.2k mesurée);commun (toujours)
R5;1;10k;R_Axial_DIN0207_L6.3mm_D2.5mm_P10.16mm_Horizontal;Pull-down base (état sûr au boot);commun (toujours)
R6;1;10k;R_Axial_DIN0207_L6.3mm_D2.5mm_P10.16mm_Horizontal;Pull-down base (état sûr au boot);profil n3pp
R29 R32 R7 R8;4;10k;R_Axial_DIN0207_L6.3mm_D2.5mm_P10.16mm_Horizontal;Pull-down base (état sûr au boot);extension (option)
R9;1;1k;R_Axial_DIN0207_L6.3mm_D2.5mm_P10.16mm_Horizontal;Résistance LED témoin (DNP si profil batterie);commun (toujours)
A1 (supports);2;Support femelle 1x15 P2.54;monte sur l'empreinte ESP32_DevKit_V1_30pin;Barrettes femelles 15 pts : le DevKit s'enfiche, jamais soudé;commun (toujours)

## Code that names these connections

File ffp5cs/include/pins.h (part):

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constexpr int ONE_WIRE_BUS = 41;  // Bus DS18B20 (37 = conflit PSRAM octale)

// I2C (Wire)
constexpr int I2C_SDA = 8;
constexpr int I2C_SCL = 9;

// OLED Display (I2C)
constexpr int OLED_SDA = I2C_SDA;
constexpr int OLED_SCL = I2C_SCL;
constexpr int OLED_ADDR = 0x3C;

// RTC DS3231 (I2C) - optionnel, pour heure précise offline
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
// SD carte (SPI) - optionnel ; broches NON câblées sur la carte porteuse
// (conservées pour compiler le support SD, à câbler via J20 le cas échéant)
constexpr int SD_CS_PIN   = 10;
constexpr int SD_MOSI_PIN = 11;
constexpr int SD_CLK_PIN  = 12;
constexpr int SD_MISO_PIN = 14;

} // namespace Pins

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// Source de vérité : pinmap_universel_propose.json. SD native (10/12/13/14),
// K5/K6 (=AUX1/AUX2) embarqués : GPIO 48 (LED RGB v1.0 : recopie d'état K5,
// cosmétique) et 45 (strapping VDD_SPI : commande via base 1k + pull-down 10k,
// sûre au boot, comme GPIO2/15 sur les cartes historiques).
namespace Pins {
constexpr int ULTRASON_AQUA = 39;  // net US1
constexpr int ULTRASON_TANK = 40;  // net US2
constexpr int ULTRASON_POTA = 41;  // net US3

constexpr int EAU_POTAGER = ULTRASON_POTA; // Alias pour rétrocompatibilité
constexpr int LUMINOSITE = 6;      // net ADC_E (ADC1_CH5)

constexpr int POMPE_AQUA   = 15;   // net K1
constexpr int POMPE_RESERV = 16;   // net K2
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constexpr int AUX1 = 48;           // net AUX1 (K5)
constexpr int AUX2 = 45;           // net AUX2 (K6)

constexpr int SERVO_GROS   = 21;   // net SERVO1
constexpr int SERVO_PETITS = 47;   // net SERVO2

constexpr int DHT_PIN      = 38;   // net DHT_INT (LED RGB v1.1 : scintillement cosmétique)
constexpr int ONE_WIRE_BUS = 42;   // net ONEWIRE

constexpr int I2C_SDA = 8;
constexpr int I2C_SCL = 9;
constexpr int OLED_SDA = I2C_SDA;
constexpr int OLED_SCL = I2C_SCL;
constexpr int OLED_ADDR = 0x3C;
constexpr uint8_t DS3231_I2C_ADDR = 0x68;

// microSD embarquée (slot bi-site de la carte, côté A2)
constexpr int SD_CS_PIN   = 10;
constexpr int SD_MOSI_PIN = 12;
constexpr int SD_CLK_PIN  = 13;
constexpr int SD_MISO_PIN = 14;

} // namespace Pins

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namespace Pins {
constexpr int ULTRASON_AQUA = 4;   // net US1 (partagé PLUIE msp)
constexpr int ULTRASON_TANK = 5;   // net US2 (partagé DHT_EXT msp)
constexpr int ULTRASON_POTA = 14;  // net US3 (= SD_CS en env wroom-sd)

constexpr int EAU_POTAGER = ULTRASON_POTA;
constexpr int LUMINOSITE = 36;     // net ADC_E (entrée seule, ADC1)

constexpr int POMPE_AQUA   = 16;   // net K1 (partagé POMPE n3pp)
constexpr int POMPE_RESERV = 17;   // net K2
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constexpr int AUX1 = 23;           // net AUX1 (K5)
constexpr int AUX2 = 25;           // net AUX2 (K6)

constexpr int SERVO_GROS   = 26;   // net SERVO1 (partagé SERVOGD msp)
constexpr int SERVO_PETITS = 27;   // net SERVO2 (partagé SERVOHB msp)

constexpr int DHT_PIN      = 15;   // net DHT_INT (commun aux 3 firmwares)
constexpr int ONE_WIRE_BUS = 2;    // net ONEWIRE (partagé TempEau msp)

constexpr int I2C_SDA = 21;
constexpr int I2C_SCL = 22;
constexpr int OLED_SDA = I2C_SDA;
constexpr int OLED_SCL = I2C_SCL;
constexpr int OLED_ADDR = 0x3C;
constexpr uint8_t DS3231_I2C_ADDR = 0x68;

// microSD (option env wroom-sd uniquement — lignes sur US3/AUX1/AUX2 + 12)
constexpr int SD_CS_PIN   = 14;
constexpr int SD_CLK_PIN  = 23;
constexpr int SD_MOSI_PIN = 25;
constexpr int SD_MISO_PIN = 12;    // strapping MTDI : ligne SANS pull-up sur la carte

} // namespace Pins

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constexpr int ONE_WIRE_BUS = 37;  // Bus DS18B20

// I2C (Wire) - Pins par défaut pour ESP32-S3 devkit. Vérifier câblage (VCC/GND/SDA/SCL) et pull-ups si OLED erratique (voir i2c_bus.cpp).
constexpr int I2C_SDA = 8;  // GPIO 8 (SDA)
constexpr int I2C_SCL = 9;  // GPIO 9 (SCL)

// OLED Display (I2C)
constexpr int OLED_SDA = I2C_SDA;
constexpr int OLED_SCL = I2C_SCL;
constexpr int OLED_ADDR = 0x3C;  // Adresse I2C de l'OLED

// RTC DS3231 (I2C) - optionnel, pour heure précise offline
constexpr uint8_t DS3231_I2C_ADDR = 0x68;

// SD carte (SPI) - optionnel, broches 10/11/12/14 (libres, non utilisées par les servos)
constexpr int SD_CS_PIN   = 10;
constexpr int SD_MOSI_PIN = 11;
constexpr int SD_CLK_PIN  = 12;
constexpr int SD_MISO_PIN = 14;

} // namespace Pins

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constexpr int ONE_WIRE_BUS = 26;

// I2C (Wire) - Pins par défaut pour ESP32. Vérifier câblage (VCC/GND/SDA/SCL) et pull-ups si OLED erratique (voir i2c_bus.cpp).
constexpr int I2C_SDA = 21;  // GPIO 21 (SDA)
constexpr int I2C_SCL = 22;  // GPIO 22 (SCL)

// OLED Display (I2C)
constexpr int OLED_SDA = I2C_SDA;
constexpr int OLED_SCL = I2C_SCL;
constexpr int OLED_ADDR = 0x3C;  // Adresse I2C de l'OLED

// RTC DS3231 (I2C) - optionnel, pour heure précise offline
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
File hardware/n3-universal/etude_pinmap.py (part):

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    "US2":      {"ffp5cs": "ULTRASON_TANK", "msp": "DHT_EXT (legacy, préférer BME280 0x77)"},
    "US3":      {"ffp5cs": "ULTRASON_POTA"},
    # capteurs partout
    "DHT_INT":  {"msp": "DHTPININT", "n3pp": "DHT", "ffp5cs": "DHT_PIN"},
    "ONEWIRE":  {"msp": "TempEau (DS18B20)", "ffp5cs": "DS18B20"},
    # power-gate (rail +3V3_SW) — bypass fermé par défaut (jumper) pour ffp5cs
    "GATE":     {"msp": "RELAIS (gate)", "n3pp": "RELAIS (gate)"},
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# ESP32-S3-DevKitC-1 44p — politique STRICTE puis PRAGMATIQUE
S3_ALL = {1, 2, 3, 4, 5, 6, 7, 8, 9, 10, 11, 12, 13, 14, 15, 16, 17, 18, 21,
          38, 39, 40, 41, 42, 45, 47, 48}
S3_ADC1 = set(range(1, 11))            # ADC1 = GPIO1..10 (ADC2 inutilisable WiFi)
S3_STRICT_EXCLUDE = {3, 45, 38, 48, 11}    # strapping (3/45), LED RGB (38/48), 11 = réserve non câblée
S3_PRAGMATIC_CAVEATS = {
    3:  "strapping JTAG-sel (sans effet hors eFuse JTAG) ; pas de pull-up sur la broche (R34 1k → base Q8)",
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# Variante « WROOM + SD universelle » : le slot microSD (unique, câblé en dur)
# monte sur des nets que msp et n3pp N'UTILISENT PAS — ils gardent donc TOUTES
# leurs fonctions, SD comprise, sans arbitrage :
#   SD_CS   = GPIO14 (net US3 — ultrason potager, ffp5cs seulement)
#   SD_CLK  = GPIO23 (net AUX1 — breakout, ffp5cs seulement)
#   SD_MOSI = GPIO25 (net AUX2 — breakout, ffp5cs seulement)
#   SD_MISO = GPIO12 (broche libre ; strapping MTDI : AUCUN pull-up, socket nu)
# Seul ffp5cs-sur-WROOM doit choisir, PAR ENV DE BUILD (mécanisme PINMAP_* déjà
# en place) : env « wroom-sd » = SD active, renonce à US_POTA + AUX1/AUX2 ;
# env standard = 3 ultrasons + AUX, pas de SD. ffp5cs-sur-S3 n'arbitre rien
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NETS_WROOM_SD["AUX2"].update({"msp": "SD_MOSI (option SD)", "n3pp": "SD_MOSI (option SD)"})
NETS_WROOM_SD["AUX2"]["ffp5cs"] = "AUX2 — ou SD_MOSI en env wroom-sd"
NETS_WROOM_SD["SD_MISO"] = {"msp": "SD_MISO", "n3pp": "SD_MISO",
                            "ffp5cs": "SD_MISO (GPIO12 : AUCUN pull-up, socket nu)"}
WROOM_SD_OPTION = {"SD_MISO": 12}

WROOM_MAP = {
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    "SERVO1": 26, "SERVO2": 27,
    "US1": 4, "US2": 5, "US3": 14,
    "DHT_INT": 15, "ONEWIRE": 2, "GATE": 13,
    # SD : absente du site WROOM (S3 uniquement) ; GPIO12 reste libre (header)
}
S3_MAP = {
    "I2C_SDA": 8, "I2C_SCL": 9,
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    "SERVO1": 21, "SERVO2": 47,
    "US1": 39, "US2": 40, "US3": 41,
    "ONEWIRE": 42,
    "GATE": 3,          # JTAG inutilisé ; R35 tire la grille de Q7 → rail +3V3_SW OFF au boot tant que GPIO3 n'est pas HAUT (ou JP1 fermé)
    "DHT_INT": 38,      # caveat LED v1.1 (cosmétique)
    "AUX1": 48,         # caveat LED v1.0 (cosmétique, breakout)
    "AUX2": 45,         # caveat strapping : entrée de module relais SANS pull-up
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
## Addendum audit final rev 0.1 (2026-08-27)

- **GPIO12/MTDI + module microSD (WROOM)** : la précaution « socket nu, aucun
  pull-up » ne couvre pas un module ENFICHÉ avec carte : le pull-up interne DAT0
  de la carte SD (et a fortiori un module tamponné type Catalex) peut tirer MTDI
  haut à l'échantillonnage du strap → VDD_SDIO 1,8 V, boot en échec. Consigne :
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
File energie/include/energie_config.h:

#pragma once
/**
 * Banc d'essai energie — configuration (ESP32-S3 + 3 x INA226).
 *
 * Voies : panneau solaire (production), batterie plomb/AGM 12 V (charge /
 * decharge), consommation des peripheriques. Shunt, courant max, sens et gain
 * sont reglables ici ET a chaud par la console serie (persistes en NVS).
 *
 * Secrets : credentials.h a la racine du depot (meme fichier que n3pp/msp) :
 * WIFI_SSIDx/WIFI_PASSx, API_KEY, API_SIG_SECRET, SMTP_*.
 */

#include "credentials.h"
#include "n3_defaults.h"

#ifndef API_SIG_SECRET
#define API_SIG_SECRET ""
#endif

// -----------------------------------------------------------------------------
// Version (source unique — cf. firmwares.manifest.json, versionSource)
// -----------------------------------------------------------------------------
#define FIRMWARE_VERSION "0.2"
#define ENERGIE_SENSOR_NAME "energie"

// -----------------------------------------------------------------------------
// Broches (ESP32-S3-DevKitC-1 N16R8 ; carte n3-universal, PINMAP_UNIVERSAL)
// GPIO33-37 interdits (PSRAM octale). Ne jamais utiliser LED_BUILTIN /
// neopixelWrite : GPIO48 = relais K5 sur n3-universal.
// -----------------------------------------------------------------------------
#define ENERGIE_PIN_SDA 8
#define ENERGIE_PIN_SCL 9
#define ENERGIE_I2C_HZ 100000UL  // 100 kHz : OLED + DS3231 + 3 INA, cables courts

// GATE du rail +3V3_SW (n3-universal, Q8 via R34) : coupe au boot si JP1 != 1-2.
// Mis a HAUT au demarrage pour alimenter les prises I2C (OLED/INA). -1 = inutilise.
#define ENERGIE_PIN_RAIL_GATE 3
#define ENERGIE_RAIL_SETTLE_MS 100

// Relais n3-universal (drivers actifs HAUT, pull-down 10 k) : forces a BAS
// (OFF) au boot pour qu'un banc monte sur la carte ne commute rien.
// K1..K4 = 15..18, K5 = 48 (= LED RGB du DevKit), K6 = 45.
#define ENERGIE_SAFE_LOW_PINS {15, 16, 17, 18, 48, 45}

// Broche ALERT des INA (non routee sur les PCB : polling 1 Hz). -1 = inutilisee.
#define ENERGIE_PIN_INA_ALERT -1

// Pont diviseur batterie de la carte n3-universal (ADC_VBAT = GPIO7, 100k/22k :
// pleine echelle ~17 V, au-dessus de l'absorption AGM 14,4-14,7 V ; l'ancien 27k
// saturait vers 14,6 V), lu en option pour comparaison avec l'INA batterie.
// -1 = desactive (DevKit nu).
#define ENERGIE_PIN_ADC_VBAT -1
#define ENERGIE_VBAT_R1 100000UL
#define ENERGIE_VBAT_R2 22000UL
#define ENERGIE_VBAT_VREF 3.3f

// -----------------------------------------------------------------------------
// Voies INA226 (adresses prevues par la doc n3-universal : 0x40 / 0x41 / 0x44)
// Shunt par defaut = module standard « R100 » (0,1 ohm) -> 0,82 A max !
// Module reel (panneau 50-80 Wc, batterie, conso) : shunt externe 5-10 mohm.
// -----------------------------------------------------------------------------
#define ENERGIE_CH_COUNT 3
#define ENERGIE_CH_PANNEAU 0
#define ENERGIE_CH_BATTERIE 1
#define ENERGIE_CH_CONSO 2

#define ENERGIE_PANNEAU_ADDR 0x40
#define ENERGIE_PANNEAU_SHUNT_OHM 0.1f
#define ENERGIE_PANNEAU_IMAX_A 0.8f
#define ENERGIE_PANNEAU_INVERT false

#define ENERGIE_BATTERIE_ADDR 0x41
#define ENERGIE_BATTERIE_SHUNT_OHM 0.1f
#define ENERGIE_BATTERIE_IMAX_A 0.8f
// Convention : courant batterie > 0 = CHARGE. Mettre true si le module est
// cable a l'envers (verifier avec la commande « dump » en charge).
#define ENERGIE_BATTERIE_INVERT false

#define ENERGIE_CONSO_ADDR 0x44
#define ENERGIE_CONSO_SHUNT_OHM 0.1f
#define ENERGIE_CONSO_IMAX_A 0.8f
#define ENERGIE_CONSO_INVERT false

// Moyennage materiel : 128 x (1,1 ms bus + 1,1 ms shunt) ~ 282 ms par resultat,
// lisse le hachage d'un regulateur PWM. Reglable par la commande « avg ».
#define ENERGIE_INA_AVG_SAMPLES 128
#define ENERGIE_INA_CONV_US 1100

// -----------------------------------------------------------------------------
// Cadences
// -----------------------------------------------------------------------------
#define ENERGIE_SAMPLE_MS 1000UL          // mesure (1 Hz)
#define ENERGIE_POST_MS 10000UL           // envoi serveur (moyennes + energie de la fenetre)
#define ENERGIE_MAX_GAP_MS 30000UL        // trou de mesure au-dela duquel on n'integre pas
#define ENERGIE_DISPLAY_MS 1000UL
#define ENERGIE_WIFI_RETRY_MS 30000UL     // nouvelle session WiFi apres echec
#define ENERGIE_SOC_SAVE_MS 900000UL      // sauvegarde NVS du SoC (15 min)

// -----------------------------------------------------------------------------
// Batterie plomb/AGM 12 V
// -----------------------------------------------------------------------------
#define ENERGIE_BAT_CAPACITY_AH 12.0f
#define ENERGIE_BAT_CHARGE_EFFICIENCY 0.90f
#define ENERGIE_BAT_REST_CURRENT_A 0.12f   // ~C/100
#define ENERGIE_BAT_REST_SECONDS 1800UL    // repos avant recalage OCV

// Alerte mail batterie basse (n3_mail, SMTP de credentials.h)
#define ENERGIE_ALERT_ENABLED 1
#define ENERGIE_ALERT_LOW_V 11.8f
#define ENERGIE_ALERT_HOLD_S 60UL
#define ENERGIE_ALERT_REARM_V 12.4f
#define ENERGIE_ALERT_COOLDOWN_S 21600UL   // 6 h
#define ENERGIE_ALERT_CHARGING_A 0.05f

// -----------------------------------------------------------------------------
// Serveur (famille « energie » de n3_serveur)
// -----------------------------------------------------------------------------
#ifdef USE_HTTPS_ENDPOINTS
#define ENERGIE_SERVER_SCHEME "https://"
#else
#define ENERGIE_SERVER_SCHEME "http://"
#endif

#ifdef TEST_MODE
#define ENERGIE_POST_URL ENERGIE_SERVER_SCHEME "iot.olution.info/energie-test/post-data"
#else
#define ENERGIE_POST_URL ENERGIE_SERVER_SCHEME "iot.olution.info/energie/post-data"
#endif

#define ENERGIE_OTA_TITLE "ENERGIE OTA"
#define ENERGIE_OTA_URL_PROD "http://iot.olution.info/ota/energie/metadata.json"
#define ENERGIE_OTA_URL_TEST "http://iot.olution.info/ota/energie-test/metadata.json"

// -----------------------------------------------------------------------------
// OLED SSD1306 (prise J13 n3-universal)
// -----------------------------------------------------------------------------
#define ENERGIE_OLED_ADDR 0x3C
